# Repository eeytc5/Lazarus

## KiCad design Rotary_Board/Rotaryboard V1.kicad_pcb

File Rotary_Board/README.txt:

This board has two rotary encoders (X & Y) and the associated passives & connector.
There's also a few diodes to create the wired-AND to generate the interrupt.

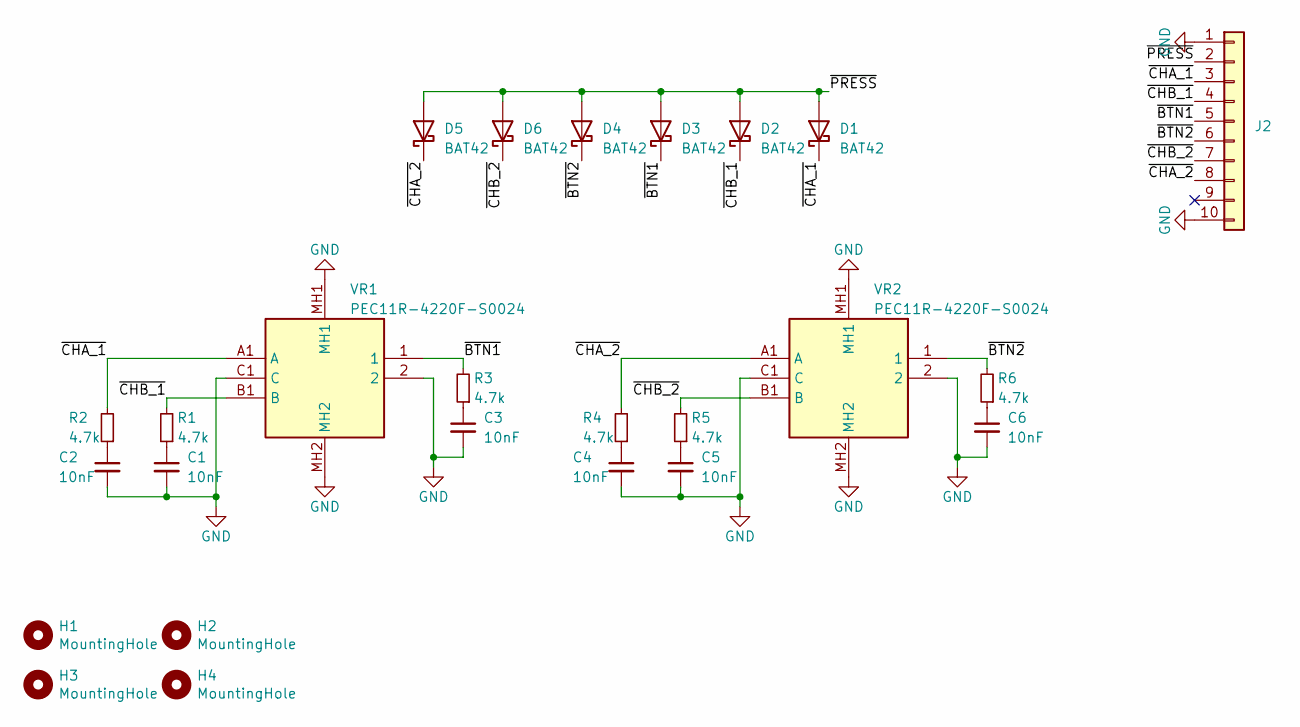
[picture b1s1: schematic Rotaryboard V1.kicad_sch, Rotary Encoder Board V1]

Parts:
C1, C2, C3, C4, C5, C6: 10nF; C_Disc_D7.5mm_W2.5mm_P5.00mm
D1, D2, D3, D4, D5, D6: BAT42; D_DO-35_SOD27_P7.62mm_Horizontal
H1, H2, H3, H4: MountingHole; MountingHole_3.2mm_M3
J2: Conn_01x10; IDC-Header_2x05_P2.54mm_Vertical
R1, R2, R3, R4, R5, R6: 4.7k; R_Axial_DIN0207_L6.3mm_D2.5mm_P7.62mm_Horizontal
VR1, VR2: PEC11R-4220F-S0024; PEC11R4220FS0024; Manufacturer_Part_Number PEC11R-4220F-S0024; Mouser Part Number 652-PEC11R-4220F-S24

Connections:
/~BTN1: D3.1 (K), R3.2, VR1.1; also elsewhere on the board
/~BTN2: D4.1 (K), R6.2, VR2.1; also elsewhere on the board
/~CHA_1: D1.1 (K), R2.2, VR1.A1 (A); also elsewhere on the board
/~CHA_2: D5.1 (K), R4.2, VR2.A1 (A); also elsewhere on the board
/~CHB_1: D2.1 (K), R1.2, VR1.B1 (B); also elsewhere on the board
/~CHB_2: D6.1 (K), R5.2, VR2.B1 (B); also elsewhere on the board
/~PRESS: D1.2 (A), D2.2 (A), D3.2 (A), D4.2 (A), D5.2 (A), D6.2 (A); also elsewhere on the board
GND: C1.2, C2.2, C3.2, C4.2, C5.2, C6.2, VR1.2, VR1.C1 (C), VR1.MH1, VR1.MH2, VR2.2, VR2.C1 (C), VR2.MH1, VR2.MH2; also elsewhere on the board
unnamed: C1.1, R1.1
unnamed: C2.1, R2.1
unnamed: C3.1, R3.1
unnamed: C4.1, R4.1
unnamed: C5.1, R5.1
unnamed: C6.1, R6.1

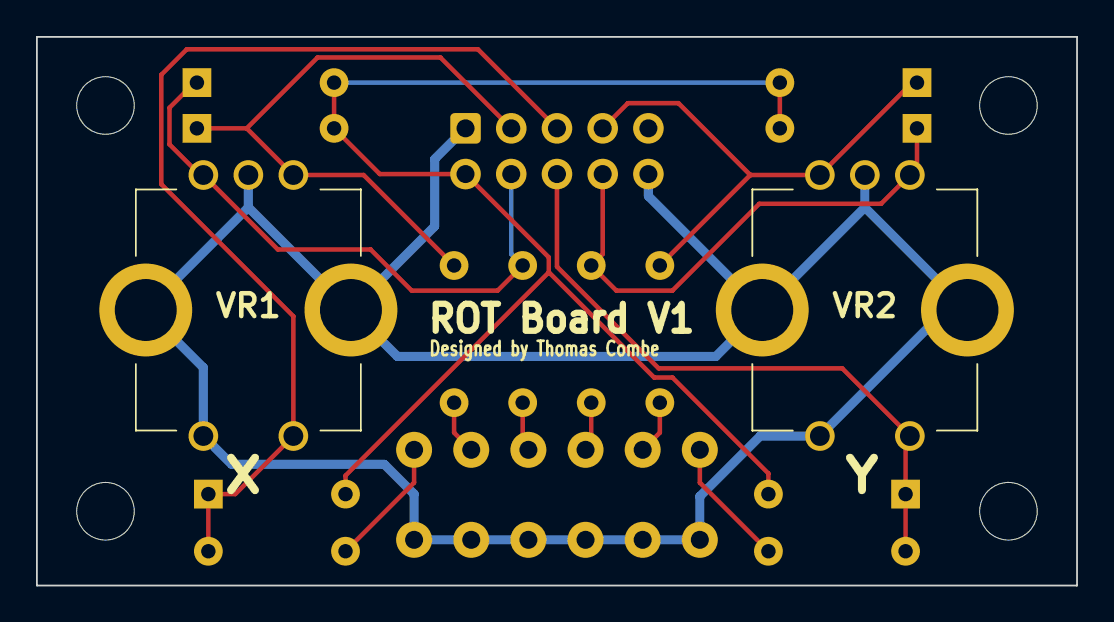
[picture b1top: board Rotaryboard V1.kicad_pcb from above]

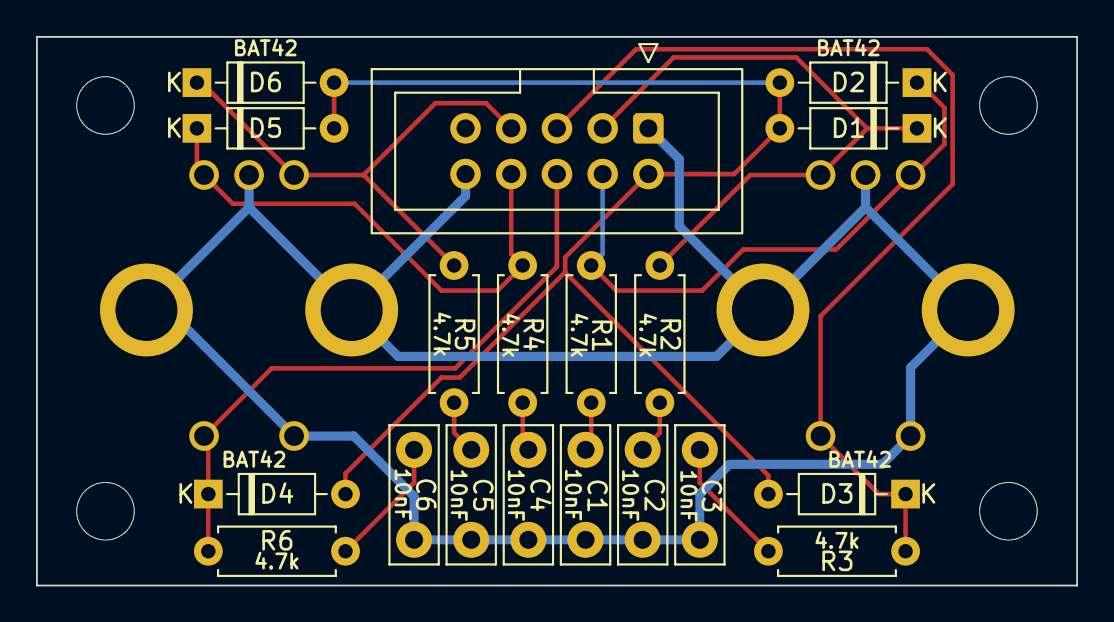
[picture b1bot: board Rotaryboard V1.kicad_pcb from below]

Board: 2 copper layers, 57.8 x 30.5 mm, 25 parts (19 on the bottom side), 14 nets.

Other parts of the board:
J1: Conn_01x10; IDC-Header_2x05_P2.54mm_Vertical

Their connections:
/~BTN1: J1.5; also elsewhere on the board
/~BTN2: J1.6; also elsewhere on the board
/~CHA_1: J1.3; also elsewhere on the board
/~CHA_2: J1.8; also elsewhere on the board
/~CHB_1: J1.4; also elsewhere on the board
/~CHB_2: J1.7; also elsewhere on the board
/~PRESS: J1.2; also elsewhere on the board
GND: J1.1, J1.10; also elsewhere on the board

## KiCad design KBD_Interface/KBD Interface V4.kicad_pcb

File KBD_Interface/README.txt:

This is a card that connects to one of the expansion ports on the motherboard. 
It interfaces the computer with the custom keyboard and two rotary encoders (X & Y).

Interacting with either the rotary encoders or the keyboard will trigger the same interrupt. 
It is up to the ISR to deduce which devices the interrupt orignated from.

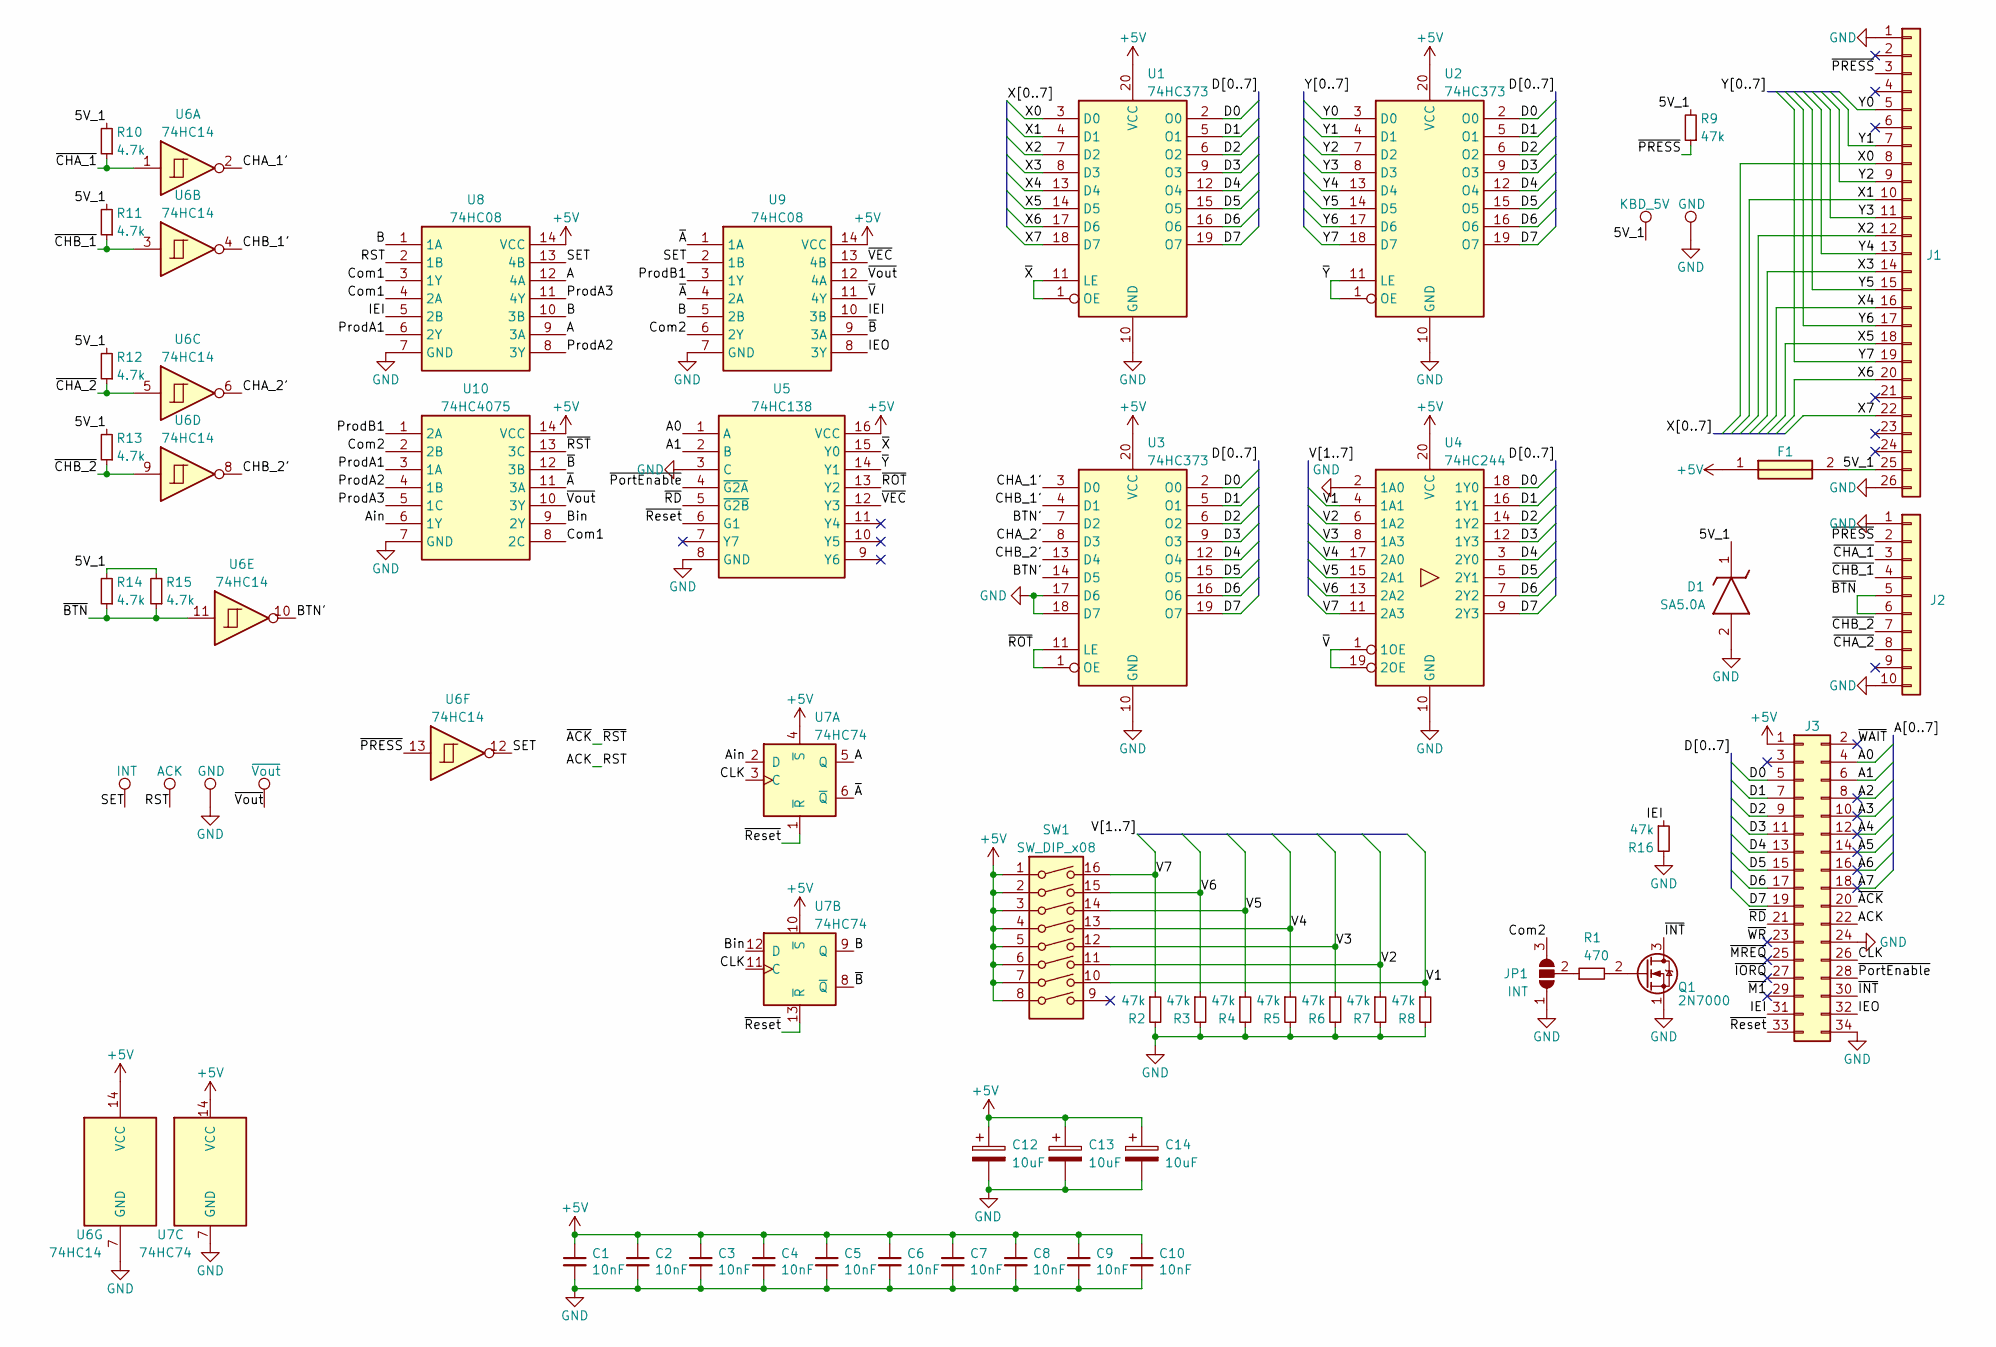
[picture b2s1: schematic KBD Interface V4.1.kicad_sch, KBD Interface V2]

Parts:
C1, C2, C3, C4, C5, C6, C7, C8, C9, C10: 10nF; C_Disc_D7.5mm_W2.5mm_P5.00mm
C12, C13, C14: 10uF; CP_Radial_D4.0mm_P1.50mm
D1: SA5.0A; D_DO-15_P12.70mm_Horizontal; Manufacturer_Part_Number SA5.0A; Mouser Part Number 576-SA5.0A
F1: 0ZRR0005FF1E; Manufacturer_Part_Number 0ZRR0005FF1E; Mouser Part Number 530-0ZRR0005FF1E
J1: Conn_01x26; IDC-Header_2x13_P2.54mm_Vertical
J2: Conn_01x10; IDC-Header_2x05_P2.54mm_Vertical
J3: Conn_02x17_Odd_Even; PinSocket_2x17_P2.54mm_Horizontal
JP1: INT; SolderJumper-3_P1.3mm_Open_RoundedPad1.0x1.5mm
Q1: 2N7000; TO-92_Inline
R1: 470; R_Axial_DIN0207_L6.3mm_D2.5mm_P2.54mm_Vertical
R2, R3, R4, R5, R6, R7, R8, R9, R16: 47k; R_Axial_DIN0207_L6.3mm_D2.5mm_P2.54mm_Vertical
R10, R11, R12, R13, R14, R15: 4.7k; R_Axial_DIN0207_L6.3mm_D2.5mm_P2.54mm_Vertical
SW1: SW_DIP_x08; DIP-16_W7.62mm_LongPads
TP3: ACK; TestPoint_Pad_D1.5mm
TP4: INT; TestPoint_Pad_D1.5mm
TP5: KBD_5V; TestPoint_Pad_D1.5mm
TP6, TP8: GND; TestPoint_Pad_1.5x1.5mm
TP7: ~{Vout}; TestPoint_Pad_D1.5mm
U1, U2, U3: 74HC373; DIP-20_W7.62mm_Socket_LongPads
U4: 74HC244; DIP-20_W7.62mm_Socket_LongPads
U5: 74HC138; DIP-16_W7.62mm_Socket_LongPads; Manufacturer_Part_Number SN74HC138N; Mouser Part Number 595-SN74HC138N
U6: 74HC14; DIP-14_W7.62mm_Socket_LongPads
U7: 74HC74; DIP-14_W7.62mm_Socket_LongPads
U8, U9: 74HC08; DIP-14_W7.62mm_Socket_LongPads; Manufacturer_Part_Number SN74HC08AN; Mouser Part Number 595-SN74HC08AN
U10: 74HC4075; DIP-14_W7.62mm_Socket_LongPads; Manufacturer_Part_Number CD74HC4075EG4

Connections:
+5V: C1.1, C2.1, C3.1, C4.1, C5.1, C6.1, C7.1, C8.1, C9.1, C10.1, C12.1, C13.1, C14.1, F1.1, J3.1, SW1.1, SW1.2, SW1.3, SW1.4, SW1.5, SW1.6, SW1.7, SW1.8, U1.20 (VCC), U2.20 (VCC), U3.20 (VCC), U4.20 (VCC), U5.16 (VCC), U6.14 (VCC), U7.4 (~S), U7.10 (~S), U7.14 (VCC), U8.14 (VCC), U9.14 (VCC), U10.14 (VCC)
/5V_1: D1.1 (K), F1.2, J1.25, R9.2, R10.2, R11.2, R12.2, R13.2, R14.2, R15.2, TP5.1
/A: U7.5 (Q), U8.9 (3A), U8.12 (4A)
/A0: J3.4, U5.1 (A)
/A1: J3.6, U5.2 (B)
/A2: J3.8
/A3: J3.10
/A4: J3.12
/A5: J3.14
/A6: J3.16
/A7: J3.18
/ACK: J3.22, TP3.1, U8.2 (1B)
/Ain: U7.2 (D), U10.6 (1Y)
/B: U7.9 (Q), U8.1 (1A), U8.10 (3B), U9.5 (2B)
/BTN': U3.7 (D2), U3.14 (D5), U6.10
/Bin: U7.12 (D), U10.9 (2Y)
/CHA_1': U3.3 (D0), U6.2
/CHA_2': U3.8 (D3), U6.6
/CHB_1': U3.4 (D1), U6.4
/CHB_2': U3.13 (D4), U6.8
/CLK: J3.26, U7.3 (C), U7.11 (C)
/Com1: U8.3 (1Y), U8.4 (2A), U10.8 (2C)
/Com2: JP1.3 (B), U9.6 (2Y), U10.2 (2B)
/D0: J3.5, U1.2 (O0), U2.2 (O0), U3.2 (O0), U4.18 (1Y0)
/D1: J3.7, U1.5 (O1), U2.5 (O1), U3.5 (O1), U4.16 (1Y1)
/D2: J3.9, U1.6 (O2), U2.6 (O2), U3.6 (O2), U4.14 (1Y2)
/D3: J3.11, U1.9 (O3), U2.9 (O3), U3.9 (O3), U4.12 (1Y3)
/D4: J3.13, U1.12 (O4), U2.12 (O4), U3.12 (O4), U4.3 (2Y0)
/D5: J3.15, U1.15 (O5), U2.15 (O5), U3.15 (O5), U4.5 (2Y1)
/D6: J3.17, U1.16 (O6), U2.16 (O6), U3.16 (O6), U4.7 (2Y2)
/D7: J3.19, U1.19 (O7), U2.19 (O7), U3.19 (O7), U4.9 (2Y3)
/IEI: J3.31, R16.1, U8.5 (2B), U9.10 (3B)
/IEO: J3.32, U9.8 (3Y)
/ProdA1: U8.6 (2Y), U10.3 (1A)
/ProdA2: U8.8 (3Y), U10.4 (1B)
/ProdA3: U8.11 (4Y), U10.5 (1C)
/ProdB1: U9.3 (1Y), U10.1 (2A)
/SET: TP4.1, U6.12, U8.13 (4B), U9.2 (1B)
/V1: R8.1, SW1.10, U4.4 (1A1)
/V2: R7.1, SW1.11, U4.6 (1A2)
/V3: R6.1, SW1.12, U4.8 (1A3)
/V4: R5.1, SW1.13, U4.17 (2A0)
/V5: R4.1, SW1.14, U4.15 (2A1)
/V6: R3.1, SW1.15, U4.13 (2A2)
/V7: R2.1, SW1.16, U4.11 (2A3)
/X0: J1.8, U1.3 (D0)
/X1: J1.10, U1.4 (D1)
/X2: J1.12, U1.7 (D2)
/X3: J1.14, U1.8 (D3)
/X4: J1.16, U1.13 (D4)
/X5: J1.18, U1.14 (D5)
/X6: J1.20, U1.17 (D6)
/X7: J1.22, U1.18 (D7)
/Y0: J1.5, U2.3 (D0)
/Y1: J1.7, U2.4 (D1)
/Y2: J1.9, U2.7 (D2)
/Y3: J1.11, U2.8 (D3)
/Y4: J1.13, U2.13 (D4)
/Y5: J1.15, U2.14 (D5)
/Y6: J1.17, U2.17 (D6)
/Y7: J1.19, U2.18 (D7)
/~ACK: J3.20, U10.13 (3C)
/~A: U7.6 (~Q), U9.1 (1A), U9.4 (2A), U10.11 (3A)
/~BTN: J2.5, J2.6, R14.1, R15.1, U6.11
/~B: U7.8 (~Q), U9.9 (3A), U10.12 (3B)
/~CHA_1: J2.3, R10.1, U6.1
/~CHA_2: J2.8, R12.1, U6.5
/~CHB_1: J2.4, R11.1, U6.3
/~CHB_2: J2.7, R13.1, U6.9
/~INT: J3.30, Q1.3 (D)
/~IORQ: J3.27
/~M1: J3.29
/~MREQ: J3.25
/~PRESS: J1.3, J2.2, R9.1, U6.13
/~PortEnable: J3.28, U5.4 (~G2A)
/~RD: J3.21, U5.5 (~G2B)
/~ROT: U3.1 (OE), U3.11 (LE), U5.13 (Y2)
/~Reset: J3.33, U5.6 (G1), U7.1 (~R), U7.13 (~R)
/~VEC: U5.12 (Y3), U9.13 (4B)
/~Vout: TP7.1, U9.12 (4A), U10.10 (3Y)
/~V: U4.1 (1OE), U4.19 (2OE), U9.11 (4Y)
/~WAIT: J3.2
/~WR: J3.23
/~X: U1.1 (OE), U1.11 (LE), U5.15 (Y0)
/~Y: U2.1 (OE), U2.11 (LE), U5.14 (Y1)
GND: C1.2, C2.2, C3.2, C4.2, C5.2, C6.2, C7.2, C8.2, C9.2, C10.2, C12.2, C13.2, C14.2, D1.2 (A), J1.1, J1.26, J2.1, J2.10, J3.24, J3.34, JP1.1 (A), Q1.1 (S), R2.2, R3.2, R4.2, R5.2, R6.2, R7.2, R8.2, R16.2, TP6.1, TP8.1, U1.10 (GND), U2.10 (GND), U3.10 (GND), U3.17 (D6), U3.18 (D7), U4.2 (1A0), U4.10 (GND), U5.3 (C), U5.8 (GND), U6.7 (GND), U7.7 (GND), U8.7 (GND), U9.7 (GND), U10.7 (GND)
unnamed: JP1.2 (C), R1.1
unnamed: Q1.2 (G), R1.2

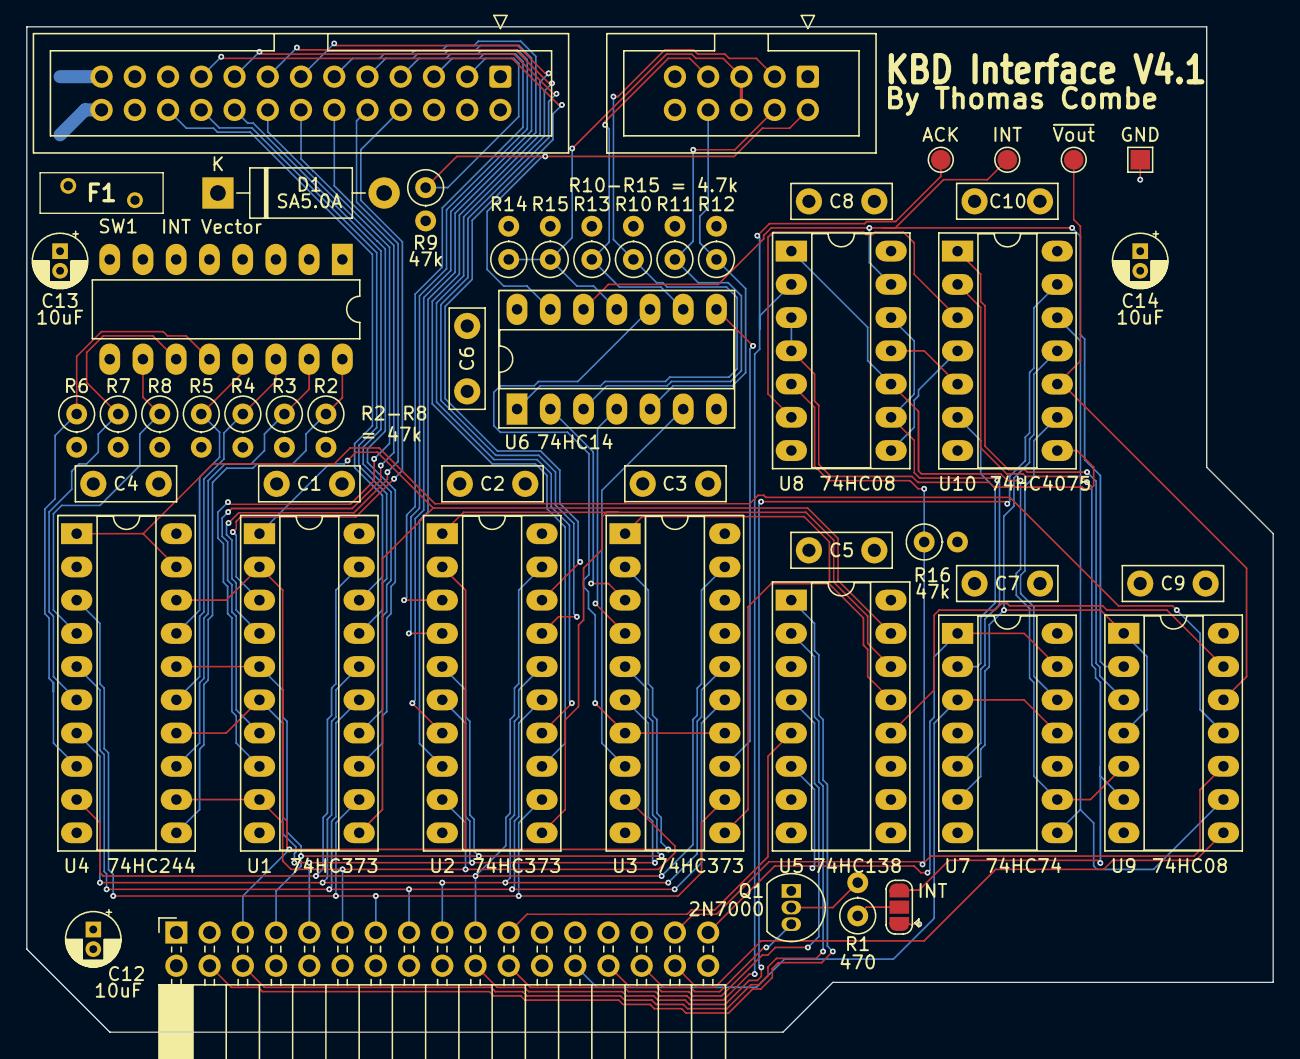
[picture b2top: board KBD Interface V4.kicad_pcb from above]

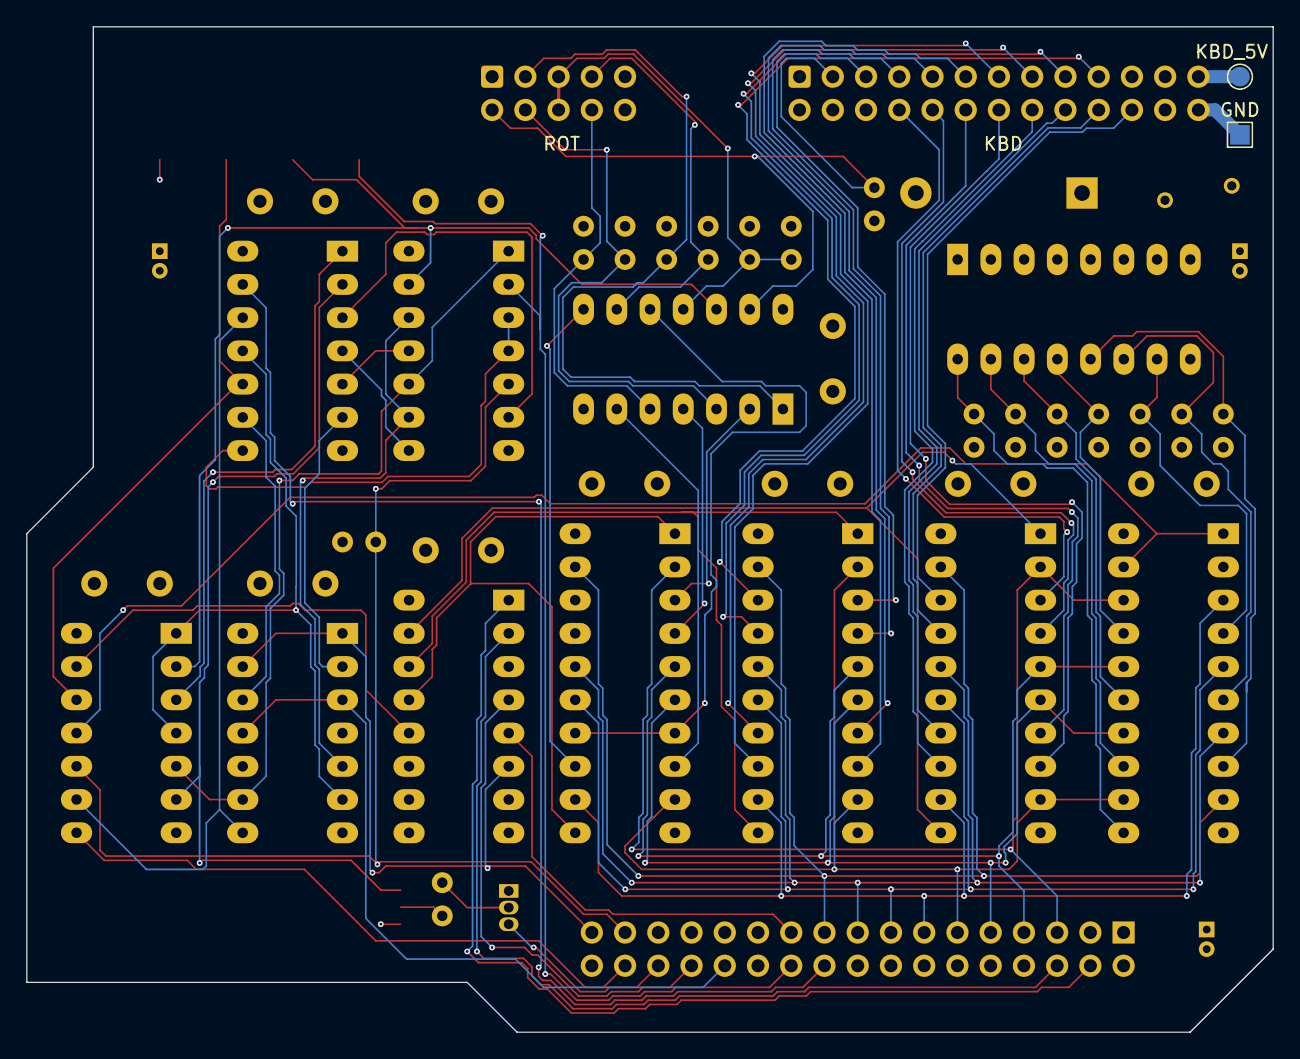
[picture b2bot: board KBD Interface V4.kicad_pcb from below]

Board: 4 copper layers, 95.2 x 76.8 mm, 53 parts (2 on the bottom side), 77 nets.

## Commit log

2025-11-03 Z80 Computer Motherboard
    Revision 1
2025-11-04 Rename Computer Board V2.1.kicad_pcb to Motherboard/Computer Board V2.1.kicad_pcb
    Moved to folder
2025-11-04 Delete Motherboard/Computer Board V2.1.kicad_pcb
    Deleted
2025-11-04 Delete Computer Board V2.1.kicad_pro
    Deleted
2025-11-04 Delete Computer Board V2.1.kicad_sch
    Deleted
2025-11-04 Delete Register.kicad_sch
    Deleted
2025-11-04 Motherboard Schematic and PCB files
2025-11-04 Created folder and README for KBD interface
2025-11-04 Keyboard Interface Schematic & PCB
2025-11-04 Rotary Board Schematic & PCB
